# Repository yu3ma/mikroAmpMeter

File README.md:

# mikroAmpMeter
Universal Current measurement device for Low power devices

Major setup in analog electronic is made by @Macola and @Dragan100 on forum:
https://forum.yu3ma.net/thread-2158-post-94918.html#pid94918

Main purpose of this analog electronics is how to measure small current signal down to uA (microAmp) and 
auto range after 5mA to biger range which support up to 2A, without interuption of current flow. This analog part 
is connected on MCU Unit. 
MCU Unit is designed for acumulating measures of current for long period of dynamic current consumption of
low-power devices like GSM enabled devices, LoRa and NB-IoT devices.

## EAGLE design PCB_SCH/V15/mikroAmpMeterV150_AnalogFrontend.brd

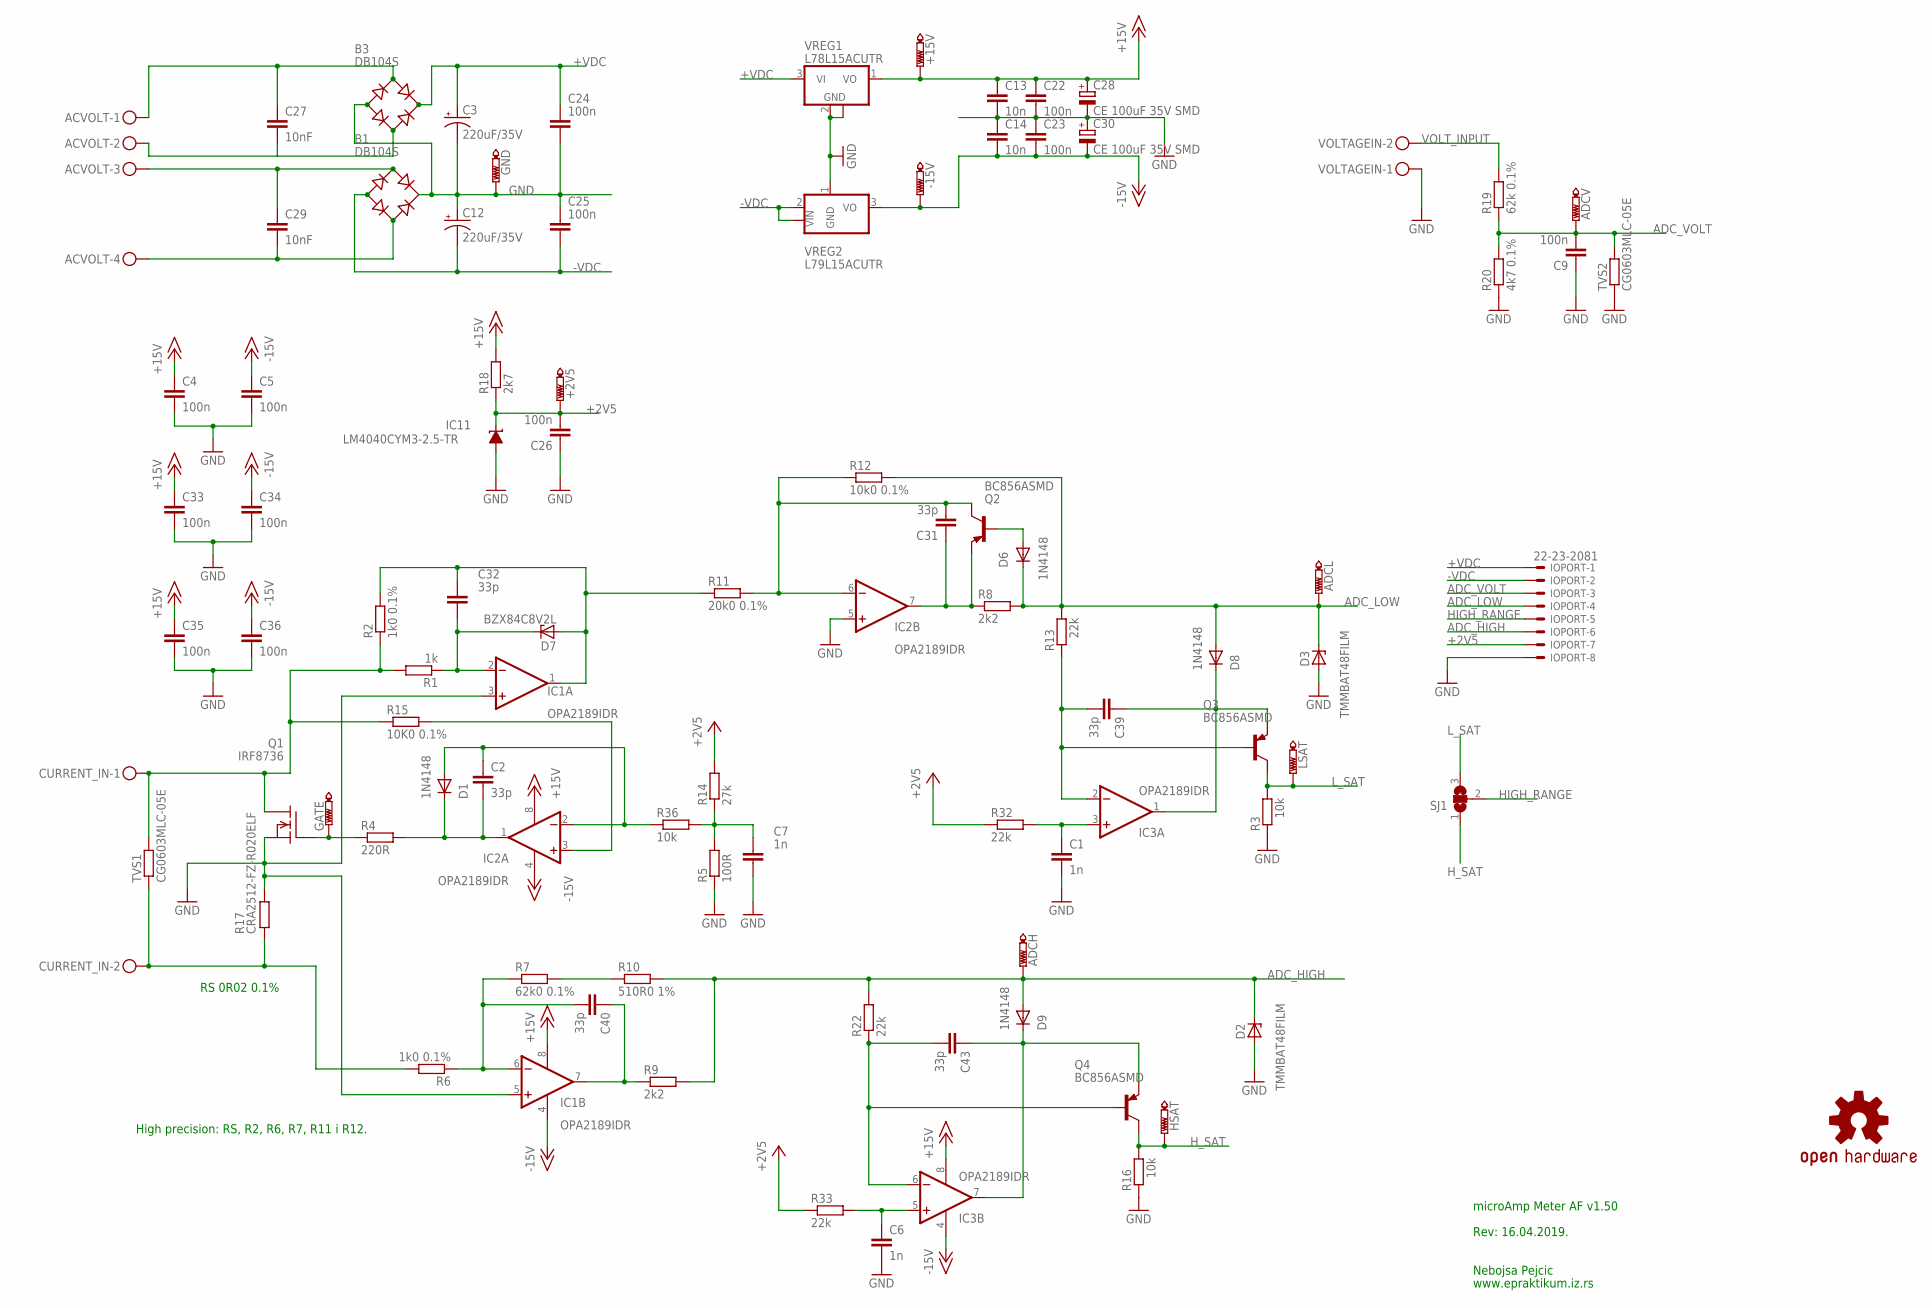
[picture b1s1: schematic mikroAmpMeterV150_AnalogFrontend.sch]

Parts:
+2V5, +15V: PTR1TP15R; TP15R
-15V: PTR1TP15R; TP15R
ACVOLT: MKDSN1,5/4-5,08
ADCH: PTR1TP15R; TP15R
ADCL: PTR1TP15R; TP15R
ADCV: PTR1TP15R; TP15R
B1, B3: DB104S; DBS
C1, C6, C7: 1n; C0805
C2, C31, C32, C39, C40, C43: 33p; C0805
C3, C12: 220uF/35V; 153CLV-1014
C4, C5, C9, C22, C23, C24, C25, C26, C33, C34, C35, C36: 100n; C0805
C13, C14: 10n; C0805
C27, C29: 10nF; C1206
C28, C30: CE 100uF 35V SMD; UD-6,3X7,7_NICHICON
CURRENT_IN: MKDSN1,5/2-5,08
D1, D6, D8, D9: 1N4148; SOD80C
D2, D3: TMMBAT48FILM; SOD80C
D7: BZX84C8V2L; SOD80C
GATE: PTR1TP15R; TP15R
GND: PTR1TP15R; TP15R
HSAT: PTR1TP15R; TP15R
IC1, IC2, IC3: OPA2189IDR; SO08@1
IC11: LM4040CYM3-2.5-TR; DBZ_R-PDSO-G3
IOPORT: 22-23-2081
LOGO1: OSHW-LOGOM; OSHW-LOGO-M
LSAT: PTR1TP15R; TP15R
Q1: IRF8736; SO-8
Q2, Q3, Q4: BC856ASMD; SOT23-BEC
R1: 1k; R0805
R2, R6: 1k0 0.1%; R0805
R3, R16, R36: 10k; R0805
R4: 220R; R0805
R5: 100R; R0805
R7: 62k0 0.1%; R0805
R8, R9: 2k2; R0805
R10: 510R0 1%; R0805
R11: 20k0 0.1%; R0805
R12: 10k0 0.1%; R0805
R13, R22, R32, R33: 22k; R0805
R14: 27k; R0805
R15: 10K0 0.1%; R0805
R17: CRA2512-FZ-R020ELF; R2512
R18: 2k7; R0805
R19: 62k 0.1%; R0805
R20: 4k7 0.1%; R0805
SJ1: SJ2W; SJ_2
TVS1, TVS2: CG0603MLC-05E; R0805
VOLTAGEIN: MKDSN1,5/2-5,08; MPN MKDSN 1,5/2-5.08
VREG1: L78L15ACUTR; SOT89
VREG2: L79L15ACUTR; SOT89

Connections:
+2V5: +2V5.TP, C26.2, IC11.1 (C), IOPORT.7, R14.2, R18.1, R32.1, R33.1
+15V: +15V.TP, C4.1, C13.1, C22.1, C28.+, C33.1, C35.1, IC1.8 (V+), IC2.8 (V+), IC3.8 (V+), R18.2, VREG1.1 (VO)
+VDC: B3.+, C3.+, C24.2, IOPORT.1, VREG1.3 (VI)
-15V: -15V.TP, C5.1, C14.2, C23.2, C30.-, C34.1, C36.1, IC1.4 (V-), IC2.4 (V-), IC3.4 (V-), VREG2.3 (VO)
-VDC: B1.-, C12.-, C25.1, IOPORT.2, VREG2.2 (VIN), VREG2.2@1 (VIN)
ADC_HIGH: ADCH.TP, D2.C, D9.A, IOPORT.6, R9.2, R10.2, R22.2
ADC_LOW: ADCL.TP, D3.C, D6.C, D8.A, IOPORT.4, R8.2, R12.2, R13.2
ADC_VOLT: ADCV.TP, C9.2, IOPORT.3, R19.1, R20.2, TVS2.2
CIN+: CURRENT_IN.1, Q1.5 (D), Q1.6 (D), Q1.7 (D), Q1.8 (D), R1.2, R2.1, R15.1, TVS1.2
CIN-: CURRENT_IN.2, R6.2, R17.1, TVS1.1
GND: B1.+, B3.-, C1.2, C3.-, C4.2, C5.2, C6.2, C7.2, C9.1, C12.+, C13.2, C14.1, C22.2, C23.1, C24.1, C25.2, C26.1, C28.-, C30.+, C33.2, C34.2, C35.2, C36.2, D2.A, D3.A, GND.TP, IC1.3 (+IN), IC1.5 (+IN), IC2.5 (+IN), IC11.2 (A), IOPORT.8, Q1.1 (S), Q1.2 (S), Q1.3 (S), R3.1, R5.1, R16.1, R17.2, R20.1, TVS2.1, VOLTAGEIN.1, VREG1.2 (GND), VREG1.2@1 (GND), VREG2.1 (GND)
HIGH_RANGE: IOPORT.5, SJ1.2
H_SAT: HSAT.TP, Q4.C, R16.2, SJ1.1
L_SAT: LSAT.TP, Q3.C, R3.2, SJ1.3
unnamed: C7.1, R5.2, R14.1, R36.2
unnamed: C32.2, D7.C, IC1.2 (-IN), R1.1
unnamed: C2.1, D1.A, IC2.2 (-IN), R36.1
unnamed: D6.A, Q2.B
unnamed: IC2.3 (+IN), R15.2
unnamed: C43.2, IC3.6 (-IN), Q4.B, R22.1
unnamed: C32.1, D7.A, IC1.1 (OUT), R2.2, R11.1
unnamed: C31.2, IC2.6 (-IN), Q2.C, R11.2, R12.1
unnamed: C31.1, IC2.7 (OUT), Q2.E, R8.1
unnamed: C39.2, IC3.2 (-IN), Q3.B, R13.1
unnamed: ACVOLT.1, B3.AC1, C27.2
unnamed: ACVOLT.2, B3.AC2, C27.1
unnamed: ACVOLT.3, B1.AC1, C29.2
unnamed: ACVOLT.4, B1.AC2, C29.1
unnamed: GATE.TP, Q1.4 (G), R4.1
unnamed: C2.2, D1.C, IC2.1 (OUT), R4.2
unnamed: C39.1, D8.C, IC3.1 (OUT), Q3.E
unnamed: C40.2, IC1.6 (-IN), R6.1, R7.1
unnamed: R7.2, R10.1
unnamed: C40.1, IC1.7 (OUT), R9.1
unnamed: C43.1, D9.C, IC3.7 (OUT), Q4.E
unnamed: C6.1, IC3.5 (+IN), R33.2
unnamed: C1.1, IC3.3 (+IN), R32.2
VOLT_INPUT: R19.2, VOLTAGEIN.2

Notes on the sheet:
microAmp Meter AF v1.50
Nebojsa Pejcic
Rev: 16.04.2019.
www.epraktikum.iz.rs
High precision: RS, R2, R6, R7, R11 i R12.
RS 0R02 0.1%

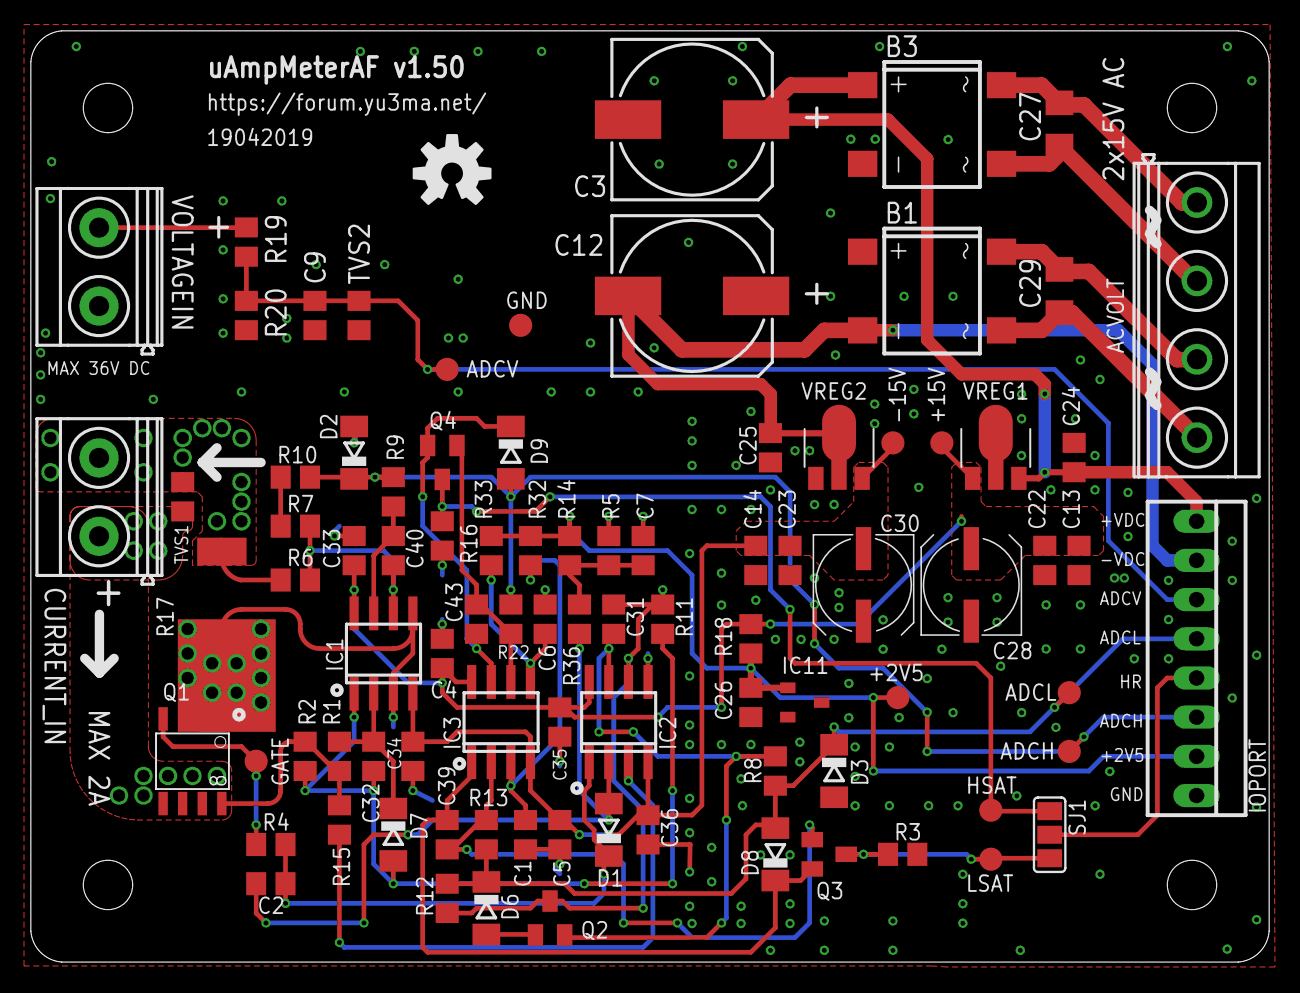
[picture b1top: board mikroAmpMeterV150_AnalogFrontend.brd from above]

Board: 2 copper layers, 80.3 x 60.4 mm, 90 parts (0 on the bottom side), 38 nets.

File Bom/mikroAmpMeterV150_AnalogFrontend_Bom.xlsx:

Partlist exported from Project mikroAmpMeterV150_AnalogFrontend.sch at 20-Apr-1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 |  |  |  |  | Kompleta za izradu | 6 | Suma za 6 kompleta [EUR] | 109.44176999999999 | Cene su bez PDV-a
Qty | Value | Device | Package | Parts | Description | Dobavljač | Oznaka | Jed Cena [EUR] | Ukupno Cena [EUR]
1 | 100R | R-EU_R0805 | R0805 | R5 | RESISTOR, European symbol | Comet | R0805 100R 1% | 0.01 | 0.01
12 | 100n | C-EUC0805 | C0805 | C4, C5, C22, C23, C33, C34, C35, C36, C9, C24, C25, C26 | CAPACITOR, European symbol | Comet | C0805 100nF 50V X7R YAG | 0.01 | 0.12
2 | 10K0 0.1% | R-EU_R0805 | R0805 | R15, R12 | RESISTOR, European symbol | Farnell | 1575900 | 0.224825 | 0.44964999999999999
3 | 10k | R-EU_R0805 | R0805 | R3, R16, R36 | RESISTOR, European symbol | Comet | R0805 10K 1% | 0.01 | 0.03
2 | 10n | C-EUC0805 | C0805 | C13, C14 | CAPACITOR, European symbol | Comet | C0805 10nF 50V X7R SAMSUNG | 1.4999999999999999E-2 | 0.03
2 | 10nF | C-EUC1206 | C1206 | C27, C29 | CAPACITOR, European symbol | Comet | C0805 10nF 50V X7R SAMSUNG | 1.4999999999999999E-2 | 0.03
4 | 1N4148 | DIODE-SOD80C | SOD80C | D1, D6, D8, D9 | DIODE | Comet | LL4148 SMD SM | 0.01 | 0.04
1 | 1k | R-EU_R0805 | R0805 | R1 | RESISTOR, European symbol | Comet | R0805 1.0K 1% YAG/ASJ | 0.01 | 0.01
2 | 1k0 0.1% | R-EU_R0805 | R0805 | R2, R6 | RESISTOR, European symbol | Farnell | 1575792 | 0.224825 | 0.44964999999999999
3 | 1n | C-EUC0805 | C0805 | C1, C6, C7 | CAPACITOR, European symbol | Comet | C0805 1.0nF 50V X7R SAMSUNG | 0.01 | 0.03
1 | 20k 0.1% | R-EU_R0805 | R0805 | R11 | RESISTOR, European symbol | Farnell | 1575937 | 0.224825 | 0.224825
1 | 220R | R-EU_R0805 | R0805 | R4 | RESISTOR, European symbol | Comet | 0805 220R 1% | 0.01 | 0.01
2 | 220uF/35V | CPOL-US153CLV-1014 | 153CLV-1014 | C3, C12 | POLARIZED CAPACITOR, American symbol | Comet | CE 220uF 35V SMD Fujicon | 0.12 | 0.24
4 | 22k | R-EU_R0805 | R0805 | R13, R22, R32, R33 | RESISTOR, European symbol | Comet | R0805 22K 1% | 0.01 | 0.04
1 | 27k | R-EU_R0805 | R0805 | R14 | RESISTOR, European symbol | Comet | R0805 27K 1% | 0.01 | 0.01
2 | 2k2 | R-EU_R0805 | R0805 | R8, R9 | RESISTOR, European symbol | Comet | R0805 2.2K 1% | 0.01 | 0.02
1 | 2k7 | R-EU_R0805 | R0805 | R18 | RESISTOR, European symbol | Comet | R0805 2.7K 1% | 0.01 | 0.01
6 | 33p | C-EUC0805 | C0805 | C2, C31, C32, C39, C40, C43 | CAPACITOR, European symbol | Comet | C0805 33pF 50V C0G SAMSUNG | 0.01 | 0.06
1 | 4k7 0.1% | R-EU_R0805 | R0805 | R20 | RESISTOR, European symbol | Farnell | 2337870 | 0.30946499999999999 | 0.30946499999999999
1 | 510R0 0.1% | R-EU_R0805 | R0805 | R10 | RESISTOR, European symbol | Farnell | 1653311 | 0.29227249999999994 | 0.29227249999999994
2 | 62k0 0.1% | R-EU_R0805 | R0805 | R7, R19 | RESISTOR, European symbol | Mouser | ERJ-PB6B6202V | 0.26519999999999999 | 0.53039999999999998
3 | BC856ASMD | BC856ASMD | SOT23-BEC | Q2, Q3, Q4 | PNP Transistror | Comet | BC856B SMD | 0.02 | 0.06
1 | BZX84C8V2L | ZENER-DIODESOD80C | SOD80C | D7 | Z-Diode | Comet | BZV55C8V2 | 0.01 | 0.01
2 | CE 100uF 35V SMD | CPOL-EUUD-6,3X7,7 | UD-6,3X7,7_NICHICON | C28, C30 | POLARIZED CAPACITOR, European symbol | Comet | CE 100uF 35V SMD Fujicon | 0.04 | 0.08
2 | CG0603MLC-05E | TVS | R0805 | TVS1, TVS2 | TVS Varistor, 8 V, 5 V, ChipGuard MLC Series | Farnell | 1838966 | 0.18118249999999997 | 0.36236499999999994
1 | 0.02R 1% 2W | R-EU_R2512 | R2512 | R17 | RESISTOR, European symbol | Comet | R2512 0.02R 1% 2W | 0.69166749999999988 | 0.69166749999999988 | Alternativa Farnell: CRA2512-FZ-R020ELF 1435948
2 | DB104S | DBLS204G | DBS | B1, B3 | Single Phase 1.0 AMP Glass Passivated Bridge Rectifier | Comet | DB107S SMD | 7.0000000000000007E-2 | 0.14000000000000001
1 | IRF8736 | IRF8736 | SO-8 | Q1 | 30V N-Channel PowerTrench TM MOSFET | Comet | IRF8736 | 0.03 | 0.03
1 | L78L15ACUTR | 78L05F | SOT89 | VREG1 | POSITIVE-VOLTAGE REGULATORS | Farnell | 2849738 | 0.12 | 0.12
1 | L79L15ACUTR | L79L15ACUTR | SOT89 | VREG2 | NEGATIVE-VOLTAGE REGULATORS | Farnell | 2849762 | 0.4 | 0.4
1 | LM4040CYM3-2.5-TR | LM4041A12DBZ | DBZ_R-PDSO-G3 | IC11 | PRECISION MICROPOWER SHUNT VOLTAGE REFERENCE | Comet | LM4040CYM3-2.5-TR | 0.3 | 0.3
2 | MKDSN1,5/2-5,08 | MKDSN1,5/2-5,08 | MKDSN1,5/2-5,08 | CURRENT_IN, VOLTAGEIN | MKDSN 1,5/ 2-5,08 Printklemme | Comet | HD-515R 2P | 0.4 | 0.8
1 | MKDSN1,5/4-5,08 | MKDSN1,5/4-5,08 | MKDSN1,5/4-5,08 | ACVOLT | MKDSN 1,5/ 4-5,08 Printklemme | Comet | HD-515R 4P | 0.8 | 0.8
3 | OPA2189IDR | OPA2189IDR | SO08@1 | IC1, IC2, IC3 | High Precision, Low Noise OPERATIONAL AMPLIFIERS | Mouser | 595-OPA2189IDR | 3.66 | 10.98
2 | TMMBAT48FILM | Shotky DIODE | SOD80C | D2, D3 | Shotky Diode | Comet | TMMBAT48 | 0.01 | 0.02
 |  |  |  |  |  |  |  |  | 0
1 | PCB | Dvoslojna plave boje | 61x81mm |  |  | JLCPCB |  | 0.5 | 0.5
 |  |  |  |  |  |  |  | SUMARNO za 1 kom | 18.240295

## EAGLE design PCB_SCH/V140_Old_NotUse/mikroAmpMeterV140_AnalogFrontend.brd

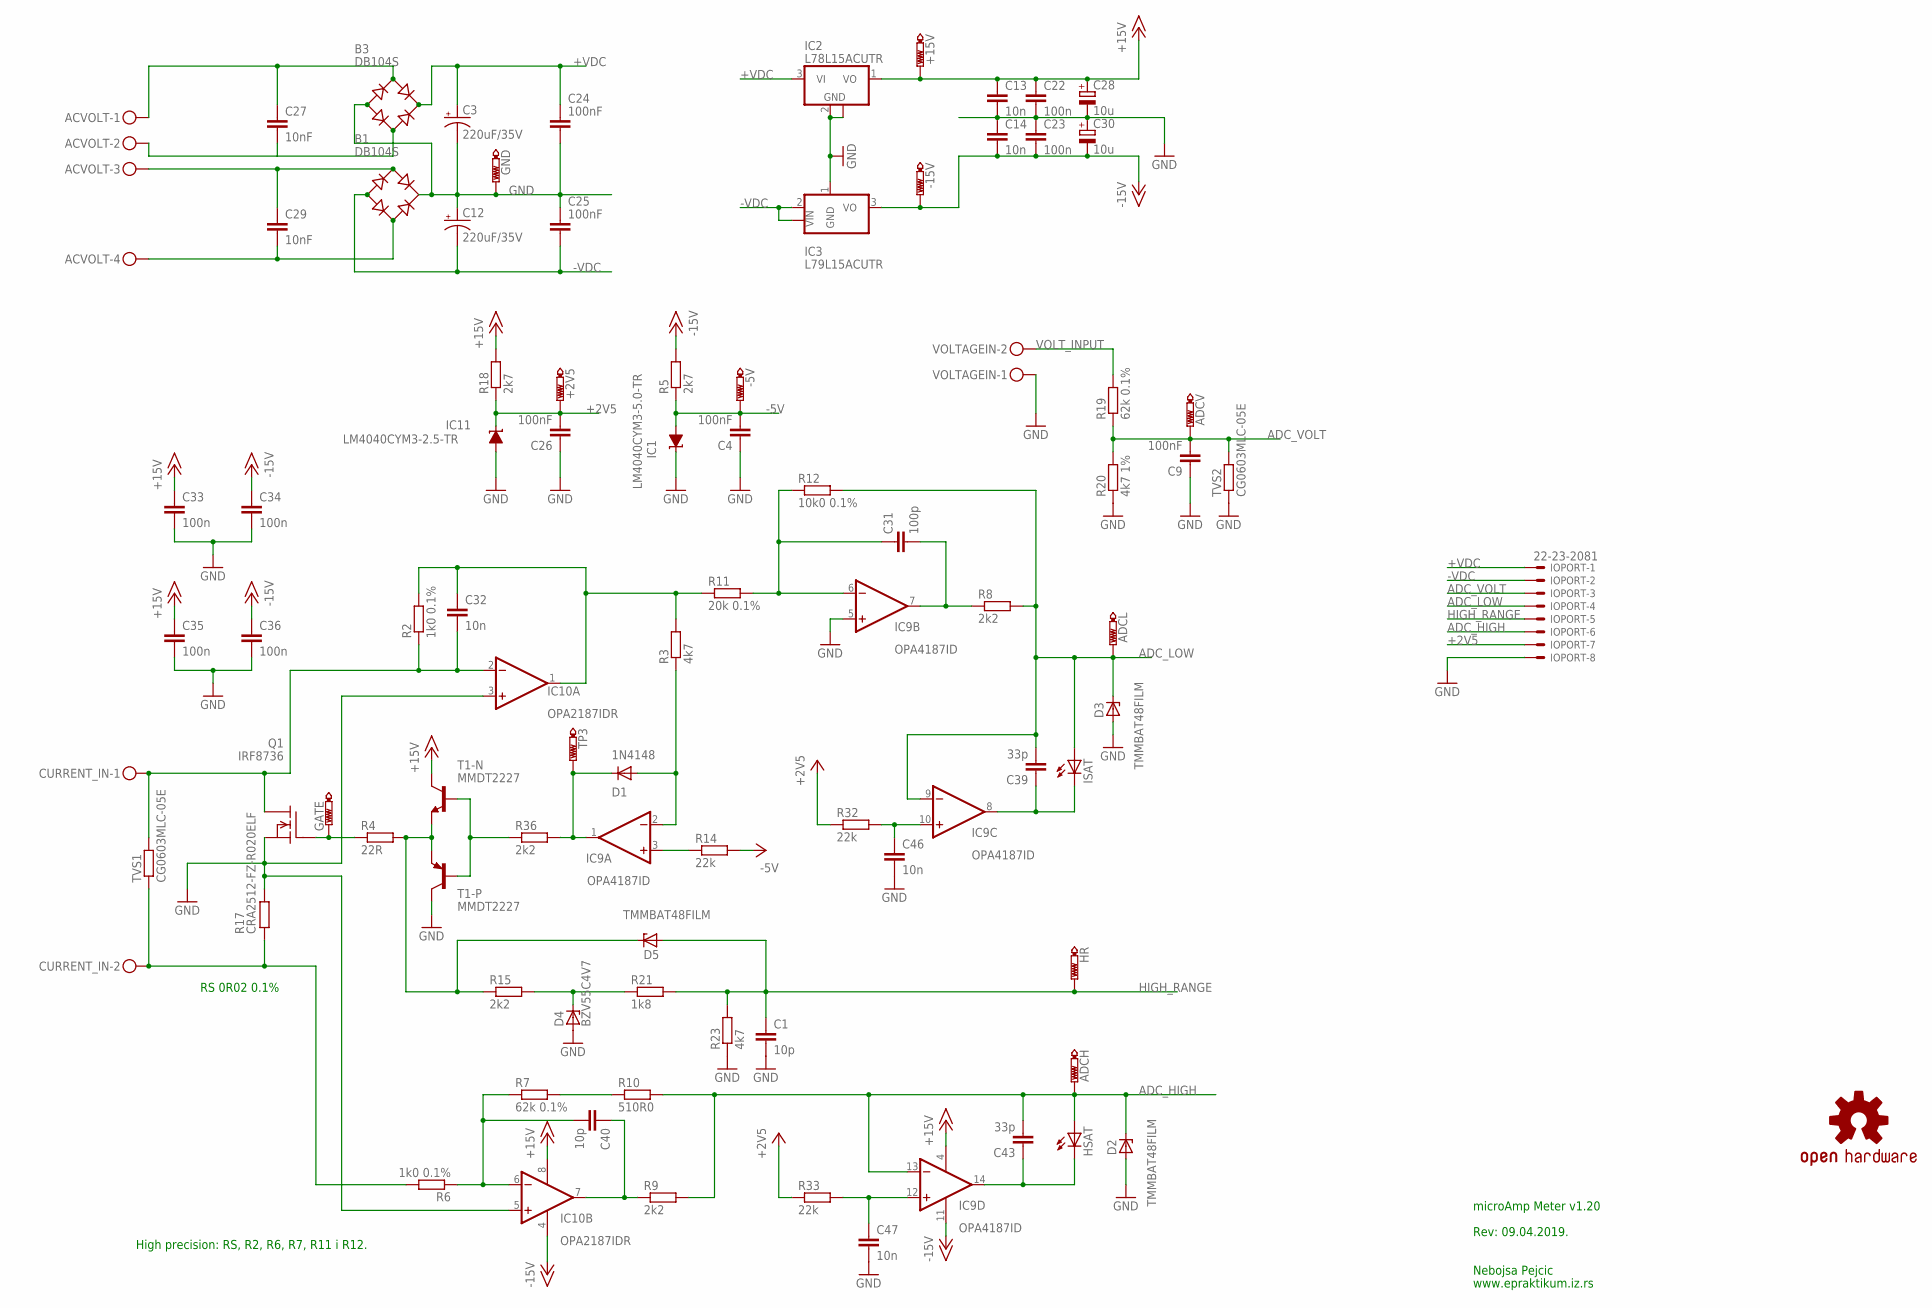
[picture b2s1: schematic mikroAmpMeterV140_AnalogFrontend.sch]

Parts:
+2V5, +15V: PTR1TP15R; TP15R
-5V, -15V: PTR1TP15R; TP15R
ACVOLT: MKDSN1,5/4-5,08
ADCH: PTR1TP15R; TP15R
ADCL: PTR1TP15R; TP15R
ADCV: PTR1TP15R; TP15R
B1, B3: DB104S; DBS
C1, C40: 10p; C0805
C3, C12: 220uF/35V; 153CLV-1014
C4, C9, C24, C25, C26: 100nF; C0805
C13, C14, C32, C46, C47: 10n; C0805
C22, C23, C33, C34, C35, C36: 100n; C0805
C27, C29: 10nF; C1206
C28, C30: 10u; UD-6,3X7,7_NICHICON
C31: 100p; C0805
C39, C43: 33p; C0805
CURRENT_IN: MKDSN1,5/2-5,08
D1: 1N4148; SOD80C
D2, D3, D5: TMMBAT48FILM; SOD80C
D4: BZV55C4V7; SOD80C
GATE: PTR1TP15R; TP15R
GND: PTR1TP15R; TP15R
HR: PTR1TP15R; TP15R
HSAT: LEDCHIPLED_1206; CHIPLED_1206
IC1: LM4040CYM3-5.0-TR; DBZ_R-PDSO-G3
IC2: L78L15ACUTR; SOT89
IC3: L79L15ACUTR; SOT89
IC9: OPA4187ID; SO14
IC10: OPA2187IDR; SO08@1
IC11: LM4040CYM3-2.5-TR; DBZ_R-PDSO-G3
IOPORT: 22-23-2081
ISAT: LEDCHIPLED_1206; CHIPLED_1206
LOGO1: OSHW-LOGOM; OSHW-LOGO-M
Q1: IRF8736; SO-8
R2, R6: 1k0 0.1%; R0805
R3, R23: 4k7; R0805
R4: 22R; R0805
R5, R18: 2k7; R0805
R7, R19: 62k 0.1%; R0805
R8, R9, R15, R36: 2k2; R0805
R10: 510R0; R0805
R11: 20k 0.1%; R0805
R12: 10k0 0.1%; R0805
R14, R32, R33: 22k; R0805
R17: CRA2512-FZ-R020ELF; R2512
R20: 4k7 1%; R0805
R21: 1k8; R0805
T1: MMDT2227; SOT363
TP3: PTR1TP15R; TP15R
TVS1, TVS2: CG0603MLC-05E; R0805
VOLTAGEIN: MKDSN1,5/2-5,08; MPN MKDSN 1,5/2-5.08

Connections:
+2V5: +2V5.TP, C26.2, IC11.1 (C), IOPORT.7, R18.1, R32.1, R33.1
+15V: +15V.TP, C13.1, C22.1, C28.+, C33.1, C35.1, IC2.1 (VO), IC9.4 (V+), IC10.8 (V+), R18.2, T1.6 (C)
+VDC: B3.+, C3.+, C24.2, IC2.3 (VI), IOPORT.1
-5V: -5V.TP, C4.2, IC1.2 (A), R5.1, R14.2
-15V: -15V.TP, C14.2, C23.2, C30.-, C34.1, C36.1, IC3.3 (VO), IC9.11 (V-), IC10.4 (V-), R5.2
-VDC: B1.-, C12.-, C25.1, IC3.2 (VIN), IC3.2@1 (VIN), IOPORT.2
ADC_HIGH: ADCH.TP, C43.2, D2.C, HSAT.A, IC9.13 (-IN), IOPORT.6, R9.2, R10.2
ADC_LOW: ADCL.TP, C39.2, D3.C, IC9.9 (-IN), IOPORT.4, ISAT.A, R8.2, R12.2
ADC_VOLT: ADCV.TP, C9.2, IOPORT.3, R19.1, R20.2, TVS2.2
CIN+: C32.2, CURRENT_IN.1, IC10.2 (-IN), Q1.5 (D), Q1.6 (D), Q1.7 (D), Q1.8 (D), R2.1, TVS1.2
CIN-: CURRENT_IN.2, R6.2, R17.1, TVS1.1
GND: B1.+, B3.-, C1.2, C3.-, C4.1, C9.1, C12.+, C13.2, C14.1, C22.2, C23.1, C24.1, C25.2, C26.1, C28.-, C30.+, C33.2, C34.2, C35.2, C36.2, C46.2, C47.2, D2.A, D3.A, D4.A, GND.TP, IC1.1 (C), IC2.2 (GND), IC2.2@1 (GND), IC3.1 (GND), IC9.5 (+IN), IC10.3 (+IN), IC10.5 (+IN), IC11.2 (A), IOPORT.8, Q1.1 (S), Q1.2 (S), Q1.3 (S), R17.2, R20.1, R23.1, T1.3 (C), TVS2.1, VOLTAGEIN.1
HIGH_RANGE: C1.1, D5.A, HR.TP, IOPORT.5, R21.2, R23.2
unnamed: IC9.3 (+IN), R14.1
unnamed: C32.1, IC10.1 (OUT), R2.2, R3.2, R11.1
unnamed: C31.1, IC9.6 (-IN), R11.2, R12.1
unnamed: C31.2, IC9.7 (OUT), R8.1
unnamed: ACVOLT.1, B3.AC1, C27.2
unnamed: ACVOLT.2, B3.AC2, C27.1
unnamed: ACVOLT.3, B1.AC1, C29.2
unnamed: ACVOLT.4, B1.AC2, C29.1
unnamed: GATE.TP, Q1.4 (G), R4.1
unnamed: D5.C, R4.2, R15.1, T1.1 (E), T1.4 (E)
unnamed: R36.1, T1.2 (B), T1.5 (B)
unnamed: D1.C, IC9.1 (OUT), R36.2, TP3.TP
unnamed: D1.A, IC9.2 (-IN), R3.1
unnamed: D4.C, R15.2, R21.1
unnamed: C39.1, IC9.8 (OUT), ISAT.C
unnamed: C40.2, IC10.6 (-IN), R6.1, R7.1
unnamed: R7.2, R10.1
unnamed: C40.1, IC10.7 (OUT), R9.1
unnamed: C43.1, HSAT.C, IC9.14 (OUT)
unnamed: C47.1, IC9.12 (+IN), R33.2
unnamed: C46.1, IC9.10 (+IN), R32.2
VOLT_INPUT: R19.2, VOLTAGEIN.2

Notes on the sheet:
microAmp Meter v1.20
Nebojsa Pejcic
Rev: 09.04.2019.
www.epraktikum.iz.rs
High precision: RS, R2, R6, R7, R11 i R12.
RS 0R02 0.1%

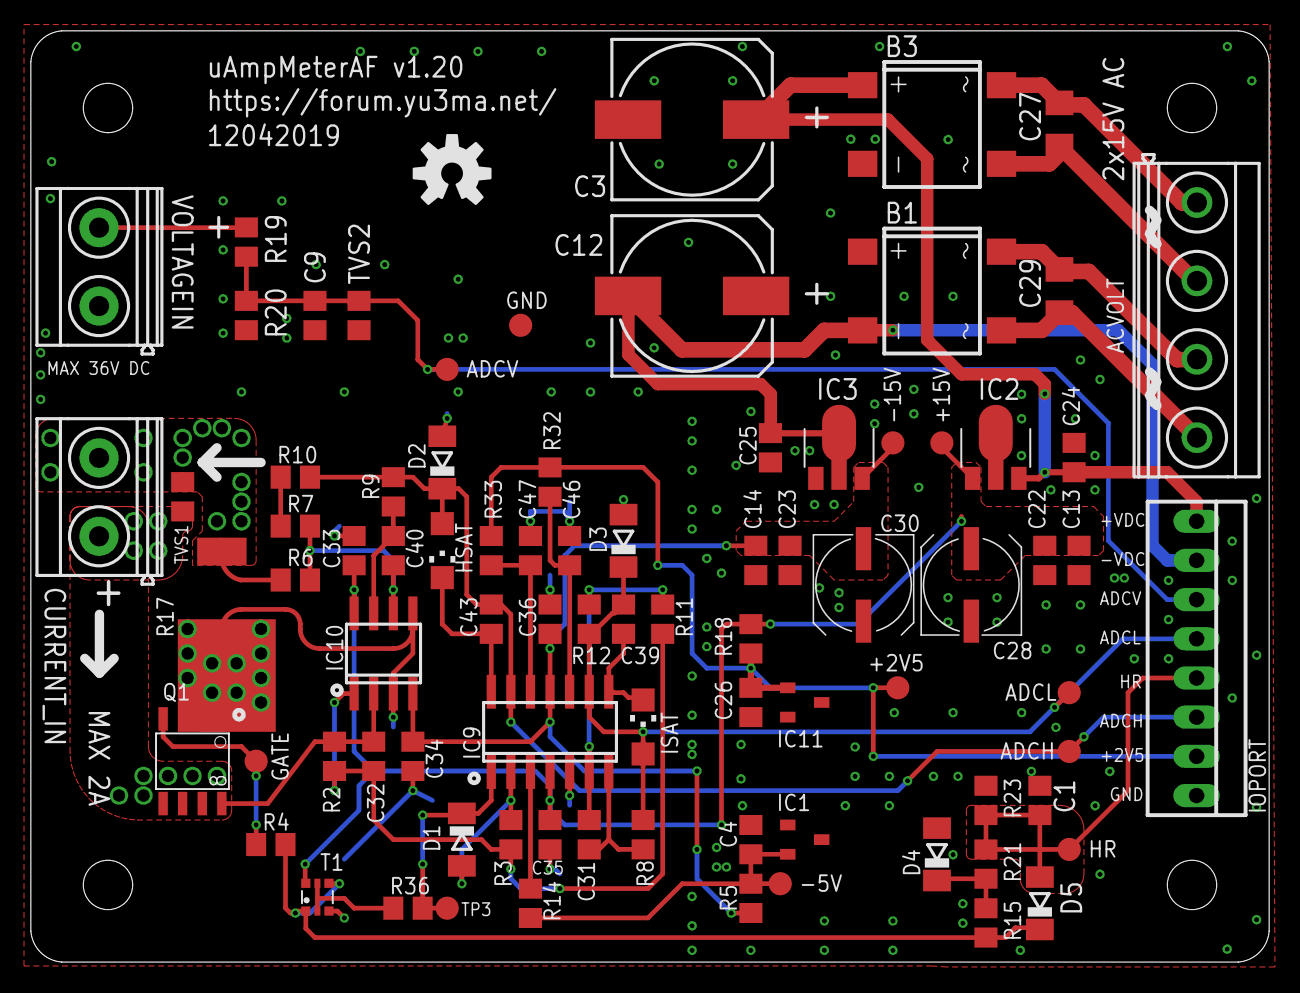
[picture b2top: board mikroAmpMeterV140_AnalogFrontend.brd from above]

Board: 2 copper layers, 80.3 x 60.4 mm, 84 parts (0 on the bottom side), 35 nets.

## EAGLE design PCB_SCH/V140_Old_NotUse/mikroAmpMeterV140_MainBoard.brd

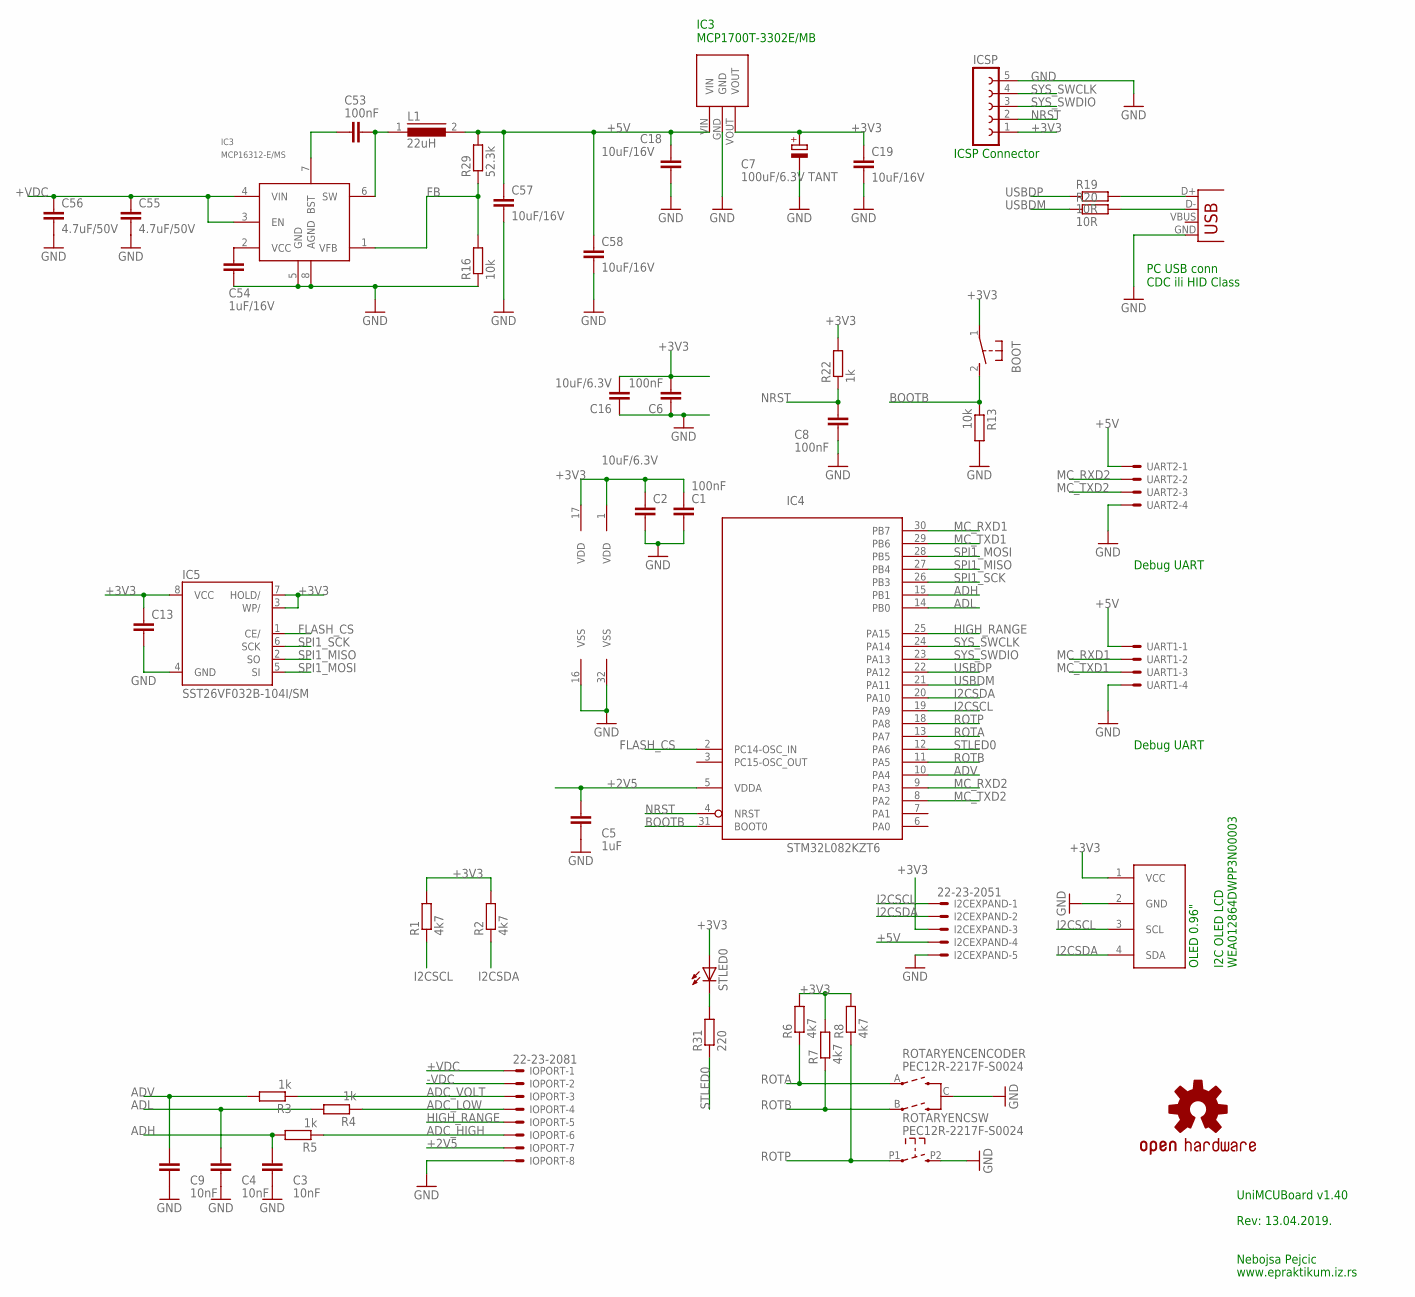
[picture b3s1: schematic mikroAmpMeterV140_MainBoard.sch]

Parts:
BOOT: 31-XX; B3F-31XX
C1, C6, C8, C53: 100nF; C0603
C2, C16: 10uF/6.3V; C0603
C3, C4, C9: 10nF; C0603
C5: 1uF; C0603
C7: 100uF/6.3V TANT; SMC_B
C13: 100n; C0603
C18, C19: 10uF/16V; C0603
C54: 1uF/16V; C0603
C55, C56: 4.7uF/50V; C1210
C57, C58: 10uF/16V; C0805
I2CEXPAND: 22-23-2051
IC3: MCP16312-E/MS; MSOP8
IC4: STM32L082KZT6; LQFP32
IC5: SST26VF032B-104I/SM; SOIC8
IC7: MCP1700T-3302E/MB; SOT89
ICSP: FE05-1
IOPORT: 22-23-2081
L1: 22uH; DR73
LOGO1: OSHW-LOGOM; OSHW-LOGO-M
OLED1: WEA012864DWPP3N00003; I2C_OLED_PACKAGE
R1, R2, R6, R7, R8: 4k7; R0603
R3, R4, R5, R22: 1k; R0603
R13: 10k; R0603
R16: 10k; R0805
R19, R20: 10R; R0603
R29: 52.3k; R0805
R31: 220; R0603
ROTARYENC: PEC12R-2217F-S0024; PEC12_INCREMENTAL_ENCODER
STLED0: LEDCHIPLED_1206; CHIPLED_1206
UART1, UART2: 22-23-2041
USB: USB-MB-S

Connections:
+2V5: C5.1, IC4.5 (VDDA), IOPORT.7
+3V3: BOOT.1, C1.1, C2.1, C6.2, C7.+, C13.2, C16.2, C19.1, I2CEXPAND.3, IC4.1 (VDD), IC4.17 (VDD), IC5.3 (WP/), IC5.7 (HOLD/), IC5.8 (VCC), IC7.VOUT, ICSP.1, OLED1.1 (VCC), R1.2, R2.2, R6.2, R7.2, R8.2, R22.2, STLED0.A
+5V: C18.1, C57.1, C58.1, I2CEXPAND.4, IC7.VIN, L1.2, R29.2, UART1.1, UART2.1
+VDC: C55.1, C56.1, IC3.3 (EN), IC3.4 (VIN), IOPORT.1
-VDC: IOPORT.2
ADC_HIGH: IOPORT.6, R5.1
ADC_LOW: IOPORT.4, R4.1
ADC_VOLT: IOPORT.3, R3.1
ADH: C3.1, IC4.15 (PB1), R5.2
ADL: C4.1, IC4.14 (PB0), R4.2
ADV: C9.1, IC4.10 (PA4), R3.2
BOOTB: BOOT.2 (S), IC4.31 (BOOT0), R13.1
FB: IC3.1 (VFB), R16.2, R29.1
FLASH_CS: IC4.2 (PC14-OSC_IN), IC5.1 (CE/)
GND: C1.2, C2.2, C3.2, C4.2, C5.2, C6.1, C7.-, C8.1, C9.2, C13.1, C16.1, C18.2, C19.2, C54.1, C55.2, C56.2, C57.2, C58.2, I2CEXPAND.5, IC3.5 (GND), IC3.8 (AGND), IC4.16 (VSS), IC4.32 (VSS), IC5.4 (GND), IC7.GND, ICSP.5, IOPORT.8, OLED1.2 (GND), R13.2, R16.1, ROTARYENC.C, ROTARYENC.P2 (2), UART1.4, UART2.4, USB.GND
HIGH_RANGE: IC4.25 (PA15), IOPORT.5
I2CSCL: I2CEXPAND.1, IC4.19 (PA9), OLED1.3 (SCL), R1.1
I2CSDA: I2CEXPAND.2, IC4.20 (PA10), OLED1.4 (SDA), R2.1
MC_RXD1: IC4.30 (PB7), UART1.2
MC_RXD2: IC4.9 (PA3), UART2.2
MC_TXD1: IC4.29 (PB6), UART1.3
MC_TXD2: IC4.8 (PA2), UART2.3
unnamed: R19.2, USB.D+
unnamed: R20.2, USB.D-
unnamed: C53.1, IC3.7 (BST)
unnamed: C54.2, IC3.2 (VCC)
NRST: C8.2, IC4.4 (NRST), ICSP.2, R22.1
ROTA: IC4.13 (PA7), R6.1, ROTARYENC.A
ROTB: IC4.11 (PA5), R7.1, ROTARYENC.B
ROTP: IC4.18 (PA8), R8.1, ROTARYENC.P1 (1)
SPI1_MISO: IC4.27 (PB4), IC5.2 (SO)
SPI1_MOSI: IC4.28 (PB5), IC5.5 (SI)
SPI1_SCK: IC4.26 (PB3), IC5.6 (SCK)
STAT_LED: R31.2, STLED0.C
STLED0: IC4.12 (PA6), R31.1
SW: C53.2, IC3.6 (SW), L1.1
SYS_SWCLK: IC4.24 (PA14), ICSP.4
SYS_SWDIO: IC4.23 (PA13), ICSP.3
USBDM: IC4.21 (PA11), R20.1
USBDP: IC4.22 (PA12), R19.1

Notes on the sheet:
ICSP Connector
IC3 MCP1700T-3302E/MB
UniMCUBoard v1.40
Nebojsa Pejcic
Rev: 13.04.2019.
www.epraktikum.iz.rs
PC USB conn CDC ili HID Class
Debug UART
I2C OLED LCD WEA012864DWPP3N00003
OLED 0.96"

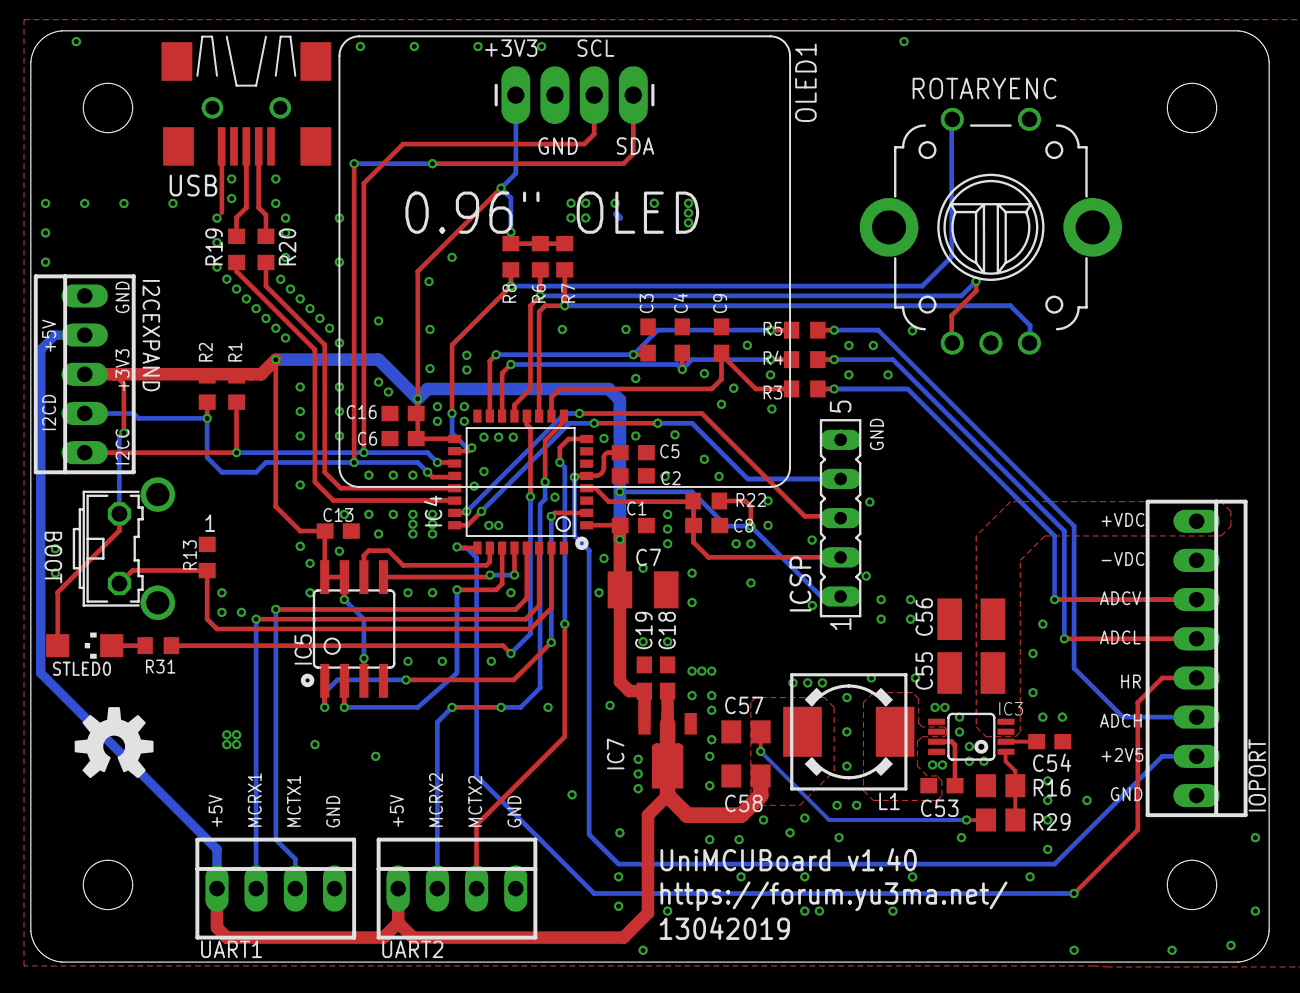
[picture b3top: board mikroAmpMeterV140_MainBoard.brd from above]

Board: 2 copper layers, 80.3 x 60.4 mm, 50 parts (0 on the bottom side), 39 nets.

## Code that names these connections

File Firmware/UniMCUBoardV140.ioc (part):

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Mcu.Name=STM32L082K(B-Z)Tx
Mcu.Package=LQFP32
Mcu.UserName=STM32L082KZTx
PA10.Mode=I2C
PA10.Signal=I2C1_SDA
PA11.Mode=Device
PA11.Signal=USB_DM
PA12.Mode=Device
PA12.Signal=USB_DP
PA13.Mode=Serial_Wire
PA13.Signal=SYS_SWDIO
PA14.Mode=Serial_Wire
PA14.Signal=SYS_SWCLK
PA15.GPIOParameters=GPIO_Label
PA15.GPIO_Label=HIGH_RANGE
PA15.Signal=GPIO_Input
PA2.GPIOParameters=GPIO_Label
PA2.GPIO_Label=MC_TXD2
PA2.Mode=Asynchronous
PA2.Signal=USART2_TX
PA3.GPIOParameters=GPIO_Label
PA3.GPIO_Label=MC_RXD2
PA3.Mode=Asynchronous
PA3.Signal=USART2_RX
PA4.GPIOParameters=GPIO_Label
PA4.GPIO_Label=ADV
PA4.Mode=IN4
PA4.Signal=ADC_IN4
PA5.GPIOParameters=GPIO_Label
PA5.GPIO_Label=ROTB
PA5.Signal=GPXTI5
PA6.GPIOParameters=GPIO_Label
PA6.GPIO_Label=STLED0
PA6.Signal=GPIO_Output
PA7.GPIOParameters=GPIO_Label
PA7.GPIO_Label=ROTA
PA7.Signal=GPXTI7
PA8.GPIOParameters=GPIO_Label
PA8.GPIO_Label=ROTP
PA8.Signal=GPIO_Input
PA9.Mode=I2C
PA9.Signal=I2C1_SCL
PB0.GPIOParameters=GPIO_Label
PB0.GPIO_Label=ADL
PB0.Mode=IN8
PB0.Signal=ADC_IN8
PB1.GPIOParameters=GPIO_Label
PB1.GPIO_Label=ADH
PB1.Mode=IN9
PB1.Signal=ADC_IN9
PB3.Mode=Full_Duplex_Master
PB3.Signal=SPI1_SCK
PB4.Mode=Full_Duplex_Master
PB4.Signal=SPI1_MISO
PB5.Mode=Full_Duplex_Master
PB5.Signal=SPI1_MOSI
PB6.GPIOParameters=GPIO_Label
PB6.GPIO_Label=MX_TXD1
PB6.Mode=Asynchronous
PB6.Signal=USART1_TX
PB7.GPIOParameters=GPIO_Label
PB7.GPIO_Label=MC_RXD1
PB7.Mode=Asynchronous
PB7.Signal=USART1_RX
PC14-OSC32_IN.GPIOParameters=GPIO_Label
PC14-OSC32_IN.GPIO_Label=FLASH_CS
PC14-OSC32_IN.Signal=GPIO_Output
RCC.SYSCLKFreq_VALUE=32000000
RCC.SYSCLKSource=RCC_SYSCLKSOURCE_PLLCLK
board=custom

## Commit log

2019-04-16 Initial commit. Version 1.4
2019-04-16 Ubacen folder sa simulacijama
2019-04-16 Licence is changed to CERN OSH and added more readme notes
2019-04-21 New version of Analog Frontend electronics V1.50. PCB design is finalised
2019-05-24 Added test firmare, device photos and some clean-up
2019-05-25 New firware version, added basic ADC measurements of Current and Voltage
2019-06-02 Implemented new Display screens for buger digits of existing measurements, implemented Average per period of time measurements and calculation, STLED0 now show Hi/Lo range

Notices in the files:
parts and their libraries:
SparkFun-Aesthetics: Licensing: Creative Commons ShareAlike 4.0 International - https://creativecommons.org/licenses/by-sa/4.0
